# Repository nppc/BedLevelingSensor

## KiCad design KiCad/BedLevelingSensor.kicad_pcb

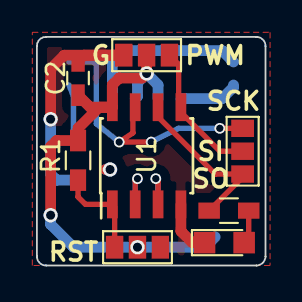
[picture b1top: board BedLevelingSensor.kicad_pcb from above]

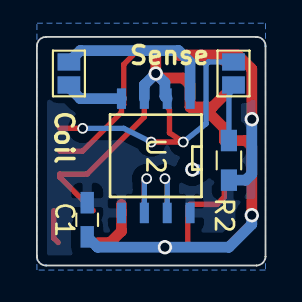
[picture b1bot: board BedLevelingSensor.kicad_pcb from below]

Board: 2 copper layers, 12.7 x 12.7 mm, 13 parts (5 on the bottom side), 12 nets.

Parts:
C1: 2.2uf; C_0603_HandSoldering
C2: 100n; C_0603_HandSoldering
D1: LED; LED_0805
J1: SOLENOID; GS2
J2: Sensor; GS2
J3: Input; GS3
J4: Prog?dat; GS3
J5: Prog?pwr; GS3
R1, R2: 10K; R_0603_HandSoldering
R3: 1K; R_0603_HandSoldering
U1: ATTINY15-1SC; SOIC-8_3.9x4.9mm_Pitch1.27mm
U2: L9110; SOIC-8-N

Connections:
GND: C1.2, C2.2, D1.1, J3.1, J5.3, R2.1, U1.4, U2.5, U2.8
IA: U1.3, U2.6
IB: U1.2, U2.7
LED: J4.3, R3.2, U1.6
MOSI: J3.3, J4.2, U1.5
unnamed: D1.2, R3.1
unnamed: J1.1, U2.4
unnamed: J1.2, U2.1
unnamed: J2.2, R2.2
RST: J5.1, R1.2, U1.1
SCK: J2.1, J4.1, U1.7
VCC: C1.1, C2.1, J3.2, J5.2, R1.1, U1.8, U2.2, U2.3

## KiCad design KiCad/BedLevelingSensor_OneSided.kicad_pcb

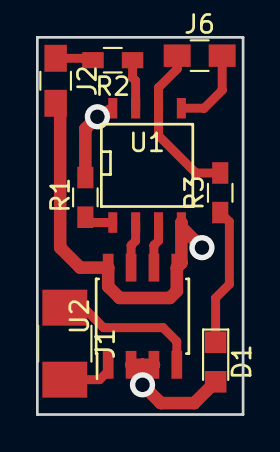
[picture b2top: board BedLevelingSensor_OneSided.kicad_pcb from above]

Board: 2 copper layers, 11.4 x 21.0 mm, 9 parts (0 on the bottom side), 12 nets.

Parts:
D1: LED; LED_0805
J1: SOLENOID; C_1210_HandSoldering
J2: Sensor; C_0805_HandSoldering
J6: Inp_data; C_0805_HandSoldering
R1: 10K; R_0603_HandSoldering
R2, R3: 1K; R_0603_HandSoldering
U1: ATTINY15-1SC; SOIC-8-N
U2: L9110; SOIC-8_3.9x4.9mm_Pitch1.27mm

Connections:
GND: J2.2, U1.4, U2.5, U2.8
IA: U1.3, U2.6
IB: U1.2, U2.7
MISO: J6.1, R3.2, U1.6
MOSI: J6.2, U1.5
unnamed: D1.1, R3.1
unnamed: J1.1, U2.4
unnamed: J1.2, U2.1
unnamed: J2.1, R2.2
RST: R1.2, U1.1
SCK: R2.1, U1.7
VCC: D1.2, R1.1, U1.8, U2.2, U2.3

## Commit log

2017-04-26 KiCad files added
2017-04-26 h-driver pdf
2017-04-27 Schematic
2017-05-10 Openscad model
2017-05-10 Schematic and PCB
2017-05-10 Schematic/PCB adjust
2017-05-11 adjust openscad model (cover and screws)
2017-05-12 adjust attiny footprint
2017-05-12 minor pcb asjust
2017-05-13 firmware initial commit
2017-05-16 continue to work on firmware...
